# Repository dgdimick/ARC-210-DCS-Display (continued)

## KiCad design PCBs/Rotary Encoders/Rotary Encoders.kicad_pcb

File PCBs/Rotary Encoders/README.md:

# ARC-210 Rotary Encoder PCB

**Last updated: November 13, 2026 at 9:41 PM MST (America/Denver)**

Version **1.4 — Final PCB design**, updated October 12, 2026.

I finalized **PCB version 1.4 and checked its physical fit** on October 12, 2026.

Version 1.4 publishes the latest saved PCB layout and project settings, including the updated board outline and v1.4 silkscreen label. I ran fresh version 1.4 checks on October 27, 2026; see the manufacturing files section. The earlier version 1.3 results below are historical.

For version 1.3, I checked this six-encoder PCB against its schematic. The electrical check reported zero errors and warnings; the PCB check reported zero violations, zero unconnected pads and zero schematic parity issues under the project's saved check settings. Courtyard and certain footprint checks are disabled in those settings.

I printed the rotary-encoder STL and confirmed that it fits, and all six encoders worked together in the combined hardware test. Testing an assembled, manufactured PCB is still on my list. The checks above cover the PCB design.

## Assembly order

**Solder the 14-pin J1 header on the back of the PCB first.** The rotary encoders will block access to the header’s solder pads once they’re installed. Install and solder the encoders after the header is in place. **Line up all the encoder pins with their holes before pressing the encoder into the PCB.** The pins bend easily and can break if forced.

## Open the project

Download this folder and keep its contents together. Open `Rotary Encoders.kicad_pro` in KiCad 10. The custom symbol and footprint libraries are included and use project-relative paths. Install KiCad's standard symbol and footprint libraries as well.

## Required 3D-printed encoder spacers

Print **six** [Rotary Encoder spacers v.1](../../Supporting%20STL%27s/Rotary_Encoder_Spacer_v.1.stl), one per encoder. They center the encoder threads in the faceplate holes.

## Optional encoder 3D model

Download [LIB_PEC11H-4220F-S0024.zip](LIB_PEC11H-4220F-S0024.zip), the original supplier library archive. Extract `PEC11H-4220F-S0024/3D/PEC11H-4220F-S0024.stp` and place the STP file beside `Rotary Encoders.kicad_pcb`.

In KiCad PCB Editor, open each encoder's Footprint Properties → 3D Models and use `${KIPRJMOD}/PEC11H-4220F-S0024.stp`. Remove or disable the older `PEC11R-4220F-S0024.stp` substitute so two models are not displayed together. Use offset X = 2.5 mm, Y = 7.49 mm, Z = 0.2300 mm; scale = 1 on all axes; rotation X = 90°, Y = -180°, Z = -180°. Check alignment in the 3D Viewer. Make the same model change in the library footprint if you want it applied to future placements.

The STEP model is optional; missing 3D models do not prevent opening or manufacturing the board.

## Parts and connections

- Six Bourns PEC11H-4220F-S0024 rotary encoders.
- J1: 14-pin header; use the assigned footprint to choose the connector.
- Both J1 pins 13 and 14 connect to GND, as do encoder common contacts and metal mounting tabs.
- The encoders' push-switch contacts S1 and S2 are deliberately unused and marked no-connect.

| J1 pin | Connection |
| --- | --- |
| 1 | SW1 B |
| 2 | SW1 A |
| 3 | SW2 A |
| 4 | SW2 B |
| 5 | SW3 B |
| 6 | SW3 A |
| 7 | SW4 A |
| 8 | SW4 B |
| 9 | SW5 B |
| 10 | SW5 A |
| 11 | SW6 B |
| 12 | SW6 A |
| 13 | GND (encoder commons and mounting tabs) |
| 14 | GND (encoder commons and mounting tabs) |

The tested GPIO pairs, identified by the labels printed on the Teensy, are: SW1 = 16/17, SW2 = 28/29, SW3 = 20/21, SW4 = 22/23, SW5 = 24/25 and SW6 = 26/27. Ensure all encoder commons share Teensy GND. The final [combined hardware test HEX](../../Firmware/Test%20Code/ARC210_Final_Hardware_Test_v1.0_Teensy41.hex) provides counts and A/B diagnostics.

## Manufacturing files

Download [Rotary-Encoder-PCB-v1.4-Gerbers-Drill.zip](Manufacturing/Rotary-Encoder-PCB-v1.4-Gerbers-Drill.zip) for PCB fabrication. Generated October 27, 2026 from the published version **1.4** PCB using KiCad 10.0.7. [Individual Gerbers, drill files, drill maps, and check reports](Manufacturing/) are also included.

The ZIP contains seven Gerber X2 layers (front/back copper, solder mask, silkscreen, and Edge.Cuts), a Gerber job file, separate metric Excellon PTH/NPTH drill files, a drill report, and manufacturing notes. Both Gerbers and drills use the absolute origin without mirroring. The source specifies a two-layer, 1.6 mm board. Verified drill totals: **65 plated holes and zero non-plated holes**; the empty NPTH file is included intentionally.

Fresh checks reported **zero ERC violations, zero non-excluded DRC violations, zero unconnected items, and zero schematic/PCB parity issues** under the saved settings. Existing disabled checks remain in effect. Review the manufacturer's preview before ordering. Testing an assembled, manufactured PCB remains pending.

PCB licensing: CERN-OHL-P-2.0, as specified in the repository.

## Teensy GPIO labels and KiCad pin numbers

**Use the numbers printed on the Teensy (or the matching GPIO labels on your breakout adapter) when following the firmware and wiring instructions.** KiCad uses a separate set of pin/pad numbers for the Teensy symbol and its matching `teensy:Teensy41` footprint. These include power and ground connections, so they are not the same as GPIO numbers.

| Teensy printed label / firmware GPIO | KiCad U1 pin / footprint pad |
| --- | ---: |
| GND (one of several ground connections) | 1 |
| 0 | 2 |
| 4 — TFT backlight | 6 |
| 14 / A0 — rotary-switch input | 36 |
| 15 / A1 — rotary-switch input | 37 |

For example, connect a rotary-switch signal to the Teensy connection marked **14/A0**, which is **KiCad pad 36**—not pad 14. In KiCad, read the symbol’s pin name and net label to identify the signal. Updating the PCB from the schematic with the matching symbol and footprint maps the connections to the correct physical locations. This pad mapping applies to the Teensy library supplied with this project; other libraries may use different numbering.

## Estimated build cost

If you’re thinking about building one, the [DIY parts purchasing estimate](../../parts/README.md#estimated-build-cost) gives you an idea of the budget, including the faceplate, display, electronics, and PCB fabrication. I’ve included the files and build notes to help you put it together.

## Questions and community builds

If you have questions, ideas, or photos of your build, I’d love to hear from you. [GitHub Discussions](https://github.com/dgdimick/ARC-210-DCS-Display/discussions)

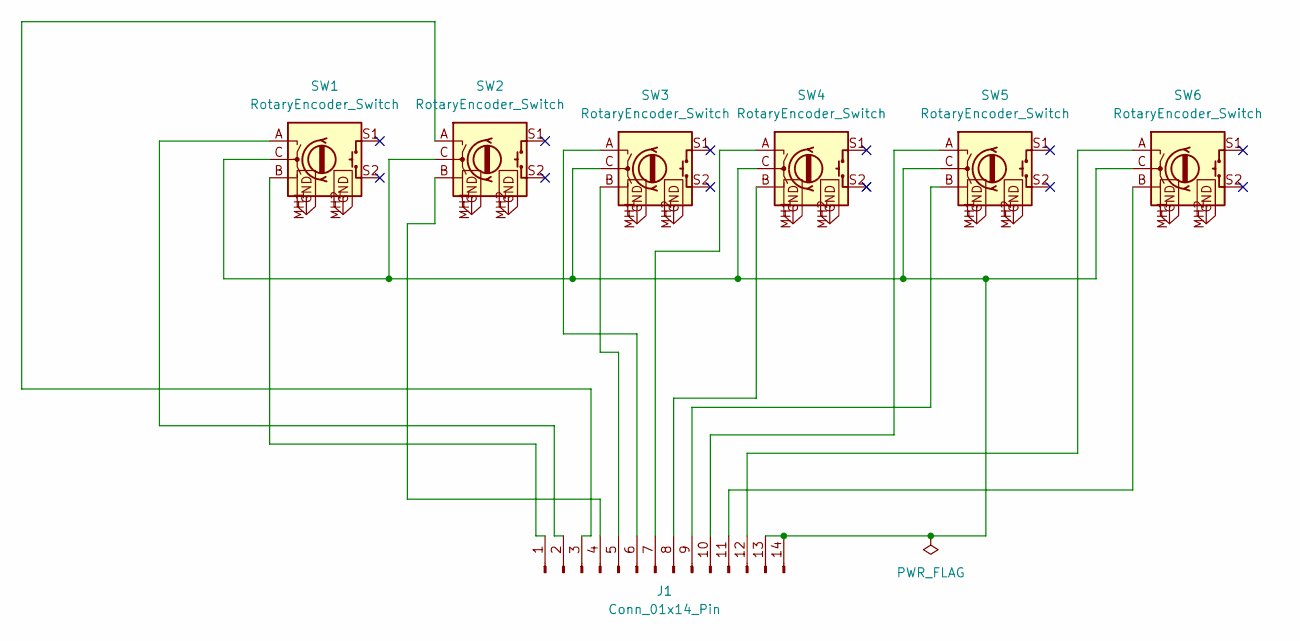
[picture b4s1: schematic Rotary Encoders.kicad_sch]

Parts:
J1: Conn_01x14_Pin; PinHeader_1x14_P2.54mm_Vertical
SW1, SW2, SW3, SW4, SW5, SW6: RotaryEncoder_Switch; PEC11H4220FS0024

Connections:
GND: SW1.MH1 (CASE), SW1.MH2 (CASE), SW2.MH1 (CASE), SW2.MH2 (CASE), SW3.MH1 (CASE), SW3.MH2 (CASE), SW4.MH1 (CASE), SW4.MH2 (CASE), SW5.MH1 (CASE), SW5.MH2 (CASE), SW6.MH1 (CASE), SW6.MH2 (CASE)
unnamed: J1.1, SW1.B
unnamed: J1.2, SW1.A
unnamed: J1.3, SW2.A
unnamed: J1.4, SW2.B
unnamed: J1.5, SW3.B
unnamed: J1.6, SW3.A
unnamed: J1.7, SW4.A
unnamed: J1.8, SW4.B
unnamed: J1.9, SW5.B
unnamed: J1.10, SW5.A
unnamed: J1.11, SW6.B
unnamed: J1.12, SW6.A
unnamed: J1.13, J1.14, SW1.C, SW2.C, SW3.C, SW4.C, SW5.C, SW6.C

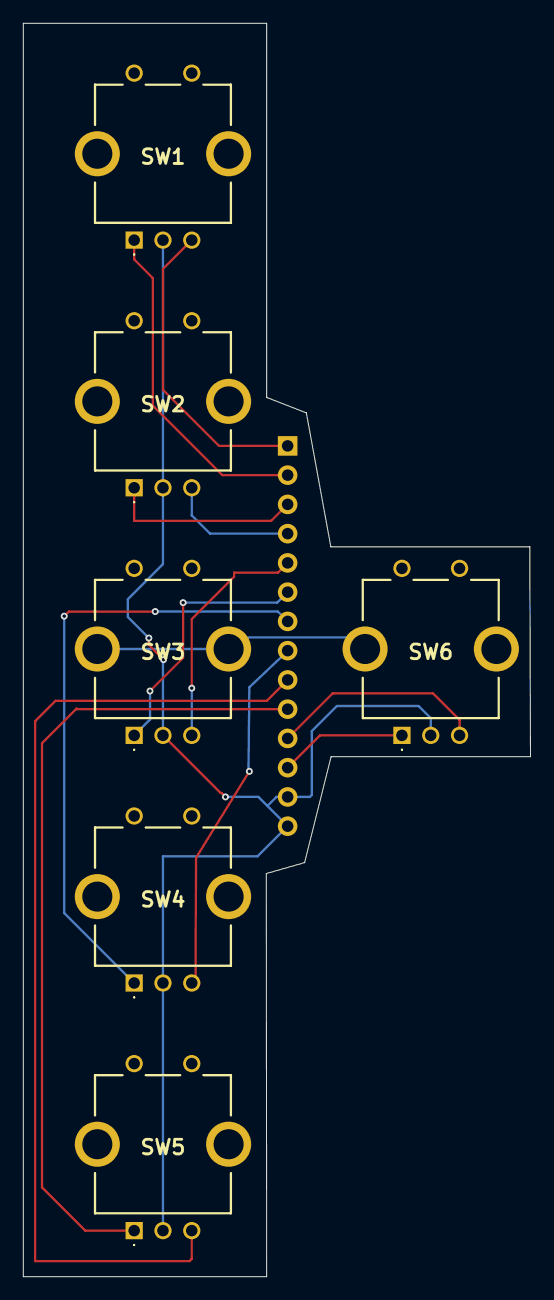
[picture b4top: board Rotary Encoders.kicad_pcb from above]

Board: 2 copper layers, 44.0 x 108.8 mm, 7 parts (1 on the bottom side), 14 nets.

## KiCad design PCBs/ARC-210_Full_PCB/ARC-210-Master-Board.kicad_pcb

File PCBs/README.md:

# ARC-210 PCBs

**Last updated: November 13, 2026 at 9:41 PM MST (America/Denver)**

Updated October 29, 2026.

## Buy a complete set of bare PCBs

See my [ARC-210 bare PCB offer and separate 3D-printing help](../Docs/ARC-210-Parts-Offers.md) for current prices, what’s included, materials, availability, shipping, VAT, and import charges. My bare PCB offer covers the ARC-210. I’ll offer printing help for the ARC-164 and ARC-186 once their printed parts are finalized. I’m happy to provide a free printed set whether you get your PCBs from me or elsewhere. Just cover shipping.

## No access to a 3D printer?

I offer separate 3D-printing help for builders whose lack of printer access is preventing their build. This supplies printed plastic only, not electronic components or a complete kit; buy the other components separately. See [ARC-210 3D-printing help](../Docs/ARC-210-Parts-Offers.md#printed-parts) for the current price, PETG colors, availability, shipping, VAT, and import-charge details.

## Estimated total build cost

I know the build cost may stretch some budgets. I’ve shared [my thoughts on the cost and development work](../parts/README.md#estimated-total-build-cost) in the parts list, including roughly 480 hours working on the code, hardware design, PCB design, and testing (about 8 hours a day) and US$500 in extra development parts. My development-time estimate includes work I did before I started using ChatGPT, as well as over 120 hours using ChatGPT and Codex to help with some of the more complex code. I’m sure my dog [Cody](../Docs/Cody%20not%20happy.jpg) isn’t happy about this.

My PCBs are designed around the faceplate and layout I’m using, so they may not fit someone else’s custom panel. I’m sharing the [source code](../Firmware/Source/Master_Program/README.md) so other builders can reuse it or adapt it to their own controls, displays, and wiring. Some changes may be needed, but I hope it gives people a useful starting point and saves them development time.

New aircraft support will require loading an updated HEX once; after that, I plan to switch between aircraft supported by that version without reflashing. This is still in development. See the [firmware version and aircraft-support plan](../Firmware/Master%20Hex%20Files/README.md).

Here are both PCB options using the same component estimates. These totals cover the panel’s parts, including the PC Flights faceplate, rather than just the bare boards. **All amounts are in US dollars (USD).**

**My PCB offer is for bare boards only.** Buy the electronic components, faceplate, and wiring separately. I’m happy to provide a free printed set whether you get your PCBs from me or elsewhere. Just cover shipping. See [what’s included and the shipping and fee details](../Docs/ARC-210-Parts-Offers.md). The build totals below cover separate DIY purchases, not a kit I sell.

| PCB purchasing option | PCB cost (USD) | Estimated full DIY build cost (USD) |
| --- | ---: | ---: |
| JLCPCB: five copies of each of four designs (20 bare boards, including spares) | US$58.20 cart estimate | US$267.72–US$300.72 |
| [My six bare PCBs only (no components)](../Docs/ARC-210-Parts-Offers.md#bare-pcb-set) | **US$40.00**, plus shipping and handling | **US$249.52–US$282.52**, before shipping, handling, and applicable fees |

For availability, what’s included in my set, and shipping/VAT/import-fee details, see [ARC-210 bare PCB offer and separate 3D-printing help](../Docs/ARC-210-Parts-Offers.md#both-pcb-purchasing-options). I’m happy to provide a free printed set whether you get your PCBs from me or elsewhere. Just cover shipping.

**My PCB-set option:** Shipping and handling are separate. I’ll only collect VAT if I’m required to; buyers may still owe import VAT, customs duties, or carrier fees even if I don’t collect VAT. Delivery and applicable fees for the other components are also separate. Compare the final delivered totals for your location.

**The US$58.20 PCB allowance uses the November 1, 2026 cart estimate: US$41.10 fabrication + US$32.10 estimated shipping − a US$15.00 coupon.** Shipping shown in that cart is already included; don’t add it twice. Coupon eligibility and shipping vary. If the US$15.00 coupon is unavailable, add US$15.00 to the JLCPCB-based estimate. Any duties, taxes, VAT, carrier fees, or other charges not included in that cart subtotal may still apply, as may delivery charges for the other components. Check your own final checkout total before ordering. These are estimates rather than fixed kit prices; the updated JLCPCB option rounds to about **US$268–US$301** for budgeting. Tools, labor, and cockpit mounting fasteners are excluded.

See the [parts-cost breakdown](../parts/README.md#estimated-build-cost) for component prices and allowances, and the [PCB manufacturing guide](../Docs/PCB-Manufacturing-JLCPCB.md) for the JLCPCB quote details. Compare the full delivered totals for your location before choosing how to buy the boards.

**SQL On/Off:** I use the **C&K A12515RNZQ solder-lug rotary switch**, with its stop ring set to **two positions for 45° total travel**. Align the knob with the panel’s ON/OFF markings. See the [parts list](../parts/README.md) for shaft-length and mounting details.

## PCB layout — five or six boards

The panel uses **five required PCBs**: one Main Board, one Button Matrix, one Rotary Encoder, and two multi-position Rotary Switch boards, all controlled by one Teensy 4.1. The **optional SQL On/Off PCB brings the total to six**; it can be omitted when wiring directly to the switch’s solder lugs. The SQL board uses the same Rotary Switch PCB design.

The [shaft spacer v.5](../Supporting%20STL%27s/Shaft_Spacer_v.5.stl) is **required in all installations** to support the longer SQL On/Off switch shaft, whether or not the optional PCB is fitted.

I’ve checked the physical fit of all four PCB designs, including the Button Matrix alignment:

| PCB | Final version | Status |
| --- | --- | --- |
| [Main Board](Master%20Board/) | 1.1 | Physical fit confirmed October 29, 2026; manufactured-board assembly and electrical testing pending |
| [Button Matrix](Button%20Matrix/) | 3.2 | Final design; v3.1 physical test fit and button alignment confirmed |
| [Rotary Encoders](Rotary%20Encoders/) | 1.4 | Final design; test fit confirmed |
| [Rotary Switches](Rotary%20Switches/) | 2.0 | Final design; test fit confirmed |

Use the KiCad project files in each linked folder. Each folder includes its wiring and assembly notes.

I’ve confirmed the mechanical fit of these designs. Testing an assembled, manufactured PCB is still on my list. Each project’s README explains the electrical checks and hardware tests completed so far.

## Required Rotary Encoder spacers

Print **six [Rotary Encoder spacers v.1](../Supporting%20STL%27s/Rotary_Encoder_Spacer_v.1.stl)**, one for each encoder, to center the encoder threads in the faceplate holes.

## Gerber and drill downloads

**Ordering for the first time?** My [JLCPCB manufacturing guide](../Docs/PCB-Manufacturing-JLCPCB.md) walks through ordering the bare boards from the manufacturer I use, including quantities, settings, and preview checks.

Button Matrix v3.2 manufacturing files generated October 30, 2026; other control-board files generated October 27, 2026; Main Board v1.1 files updated October 29, 2026:

| PCB | Version | Gerber and drill ZIP | Individual files and reports |
| --- | --- | --- | --- |
| Main Board | 1.1 | [Download ZIP](Master%20Board/Manufacturing/Main-Board-PCB-v1.1-Gerbers-Drill.zip) | [Browse files](Master%20Board/Manufacturing/) |
| Button Matrix | 3.2 | [Download ZIP](Button%20Matrix/Manufacturing/Button-Matrix-PCB-v3.2-Gerbers-Drill.zip) | [Browse files](Button%20Matrix/Manufacturing/) |
| Rotary Encoders | 1.4 | [Download ZIP](Rotary%20Encoders/Manufacturing/Rotary-Encoder-PCB-v1.4-Gerbers-Drill.zip) | [Browse files](Rotary%20Encoders/Manufacturing/) |
| Rotary Switches | 2.0 | [Download ZIP](Rotary%20Switches/Manufacturing/Rotary-Switch-PCB-v2.0-Gerbers-Drill.zip) | [Browse files](Rotary%20Switches/Manufacturing/) |

Each ZIP includes copper, solder-mask, silkscreen, and board-outline Gerbers, a Gerber job file, separate plated/non-plated Excellon drill files, a drill report, and manufacturing notes. Drill maps and ERC/DRC reports are available in each manufacturing folder.

Review the manufacturer's preview before ordering. The Button Matrix's printed fit check confirmed button alignment, and its slightly long edges were shortened for final v3.1. Manufactured-board testing remains pending for all four designs. Existing check exclusions and disabled categories are documented in the individual project READMEs and reports.

## Button Matrix PCB — version 3.2

**The current Button Matrix PCB v3.2 does not support LED backlighting.** I would need to redesign the button board with LED support, use suitable light-transmitting buttons, and make the required Main Board, power, and driver changes. I may revisit this after completing the ARC-164 and ARC-186 projects; there is no finished backlit button-board design or release date yet. See [Future Thoughts](../Docs/Future-Thoughts.md) for the lighting redesign plan.

**October 30, 2026:** v3.2 removes the duplicate SQL hole outline, retains the 12 mm NPTH, updates revision markings, and moves H3’s reference clear of the mask opening. Fresh KiCad exports and ERC/DRC checks pass under saved settings. No electrical changes; manufactured-board testing remains pending. The v3.1 notes below record the earlier outline and physical-fit work.

**Final design; v3.1 test fit confirmed — October 27, 2026:** The printed fit check confirmed that the buttons are correctly positioned. The slightly long board edges were shortened, and version **3.1** replaced v3.0 before the v3.2 hole correction. The physical test fit of the revised v3.1 board is confirmed. The updated KiCad and manufacturing files are uploaded.

The current unlit 16-button, 4 × 4 Button Matrix PCB is **version 3.2**. See the [Button Matrix README](Button%20Matrix/README.md) for front and back layout previews. The front carries the push-button switches; the back carries the matrix diodes and row/column connectors. A 12 mm pass-through provides clearance for the SQL On/Off switch.

The downloadable [version 3.2 KiCad files](Button%20Matrix/) now include the PCB layout, schematic, project settings, and custom 12 mm footprint library. The PCB includes routing; unused floating copper fills were removed. Checks found zero ERC violations, zero DRC errors, no unconnected items, and no schematic/PCB parity issues; DRC also reports zero warnings after removal of those fills. Physical fit and button alignment have been checked; manufactured-board assembly and electrical testing remain pending. A backlit version would require a redesigned button board; it is a possible future project, with no finished design or release date.

## Main Board PCB v1.1 and schematic

**Layout progress — October 28, 2026:** Component placement and routing are progressing on the Main Board. The [new Main Board layout picture](../images/Main-PCB-Layout-2026-10-28.png) shows the Teensy 4.1, TFT and control connectors, SQL On/Off solder connections, and back-side component arrangement. J9 is labelled **MODE** and J10 **MASTER**. A 26.2 mm circle provides a SQL switch body spacing guide without electrical pads. The rotary-switch mounting opening, anti-rotation slot, and four 3.5 mm mounting holes remain.

The current saved Main Board PCB and schematic have now been uploaded to match the layout-progress picture. October 29 checks after correcting the J4/TP1 values report zero ERC violations, zero DRC violations, zero unconnected items, and zero schematic/PCB mismatches under the saved settings. See the [Main Board README and picture](Master%20Board/README.md#main-pcb-3d-preview) and [3D Viewer instructions](Master%20Board/README.md#teensy-41-in-the-3d-viewer). I’ve checked the physical fit of Main Board v1.1. Final placement/routing review and current verification remain to be completed; the October 29 ERC/DRC and parity checks pass under the saved settings. Main Board v1.1 Gerber and drill files are now available above; physical fit is confirmed and manufactured-board testing remains pending.

The updated [Main Board PCB draft, schematic, and KiCad project](Master%20Board/) are available to download. The board now uses USB power and the Teensy's 3.3 V supply for TFT VCC; the external protected 5 V branch and power selector are removed. C5/C6 have been removed to match the tested direct TFT wiring; C1/C2 rotary-input filters remain. I’ve tested the TFT at 3.3 V and found the brightness satisfactory. Components are on B.Cu, facing away from the faceplate. The draft has zero unconnected items under the October 29 checks. I’ve checked the physical fit of Main Board v1.1. Final placement/routing review and current verification remain pending; Main Board v1.1 manufacturing files are provided above.

## Teensy GPIO labels and KiCad pin numbers

**Use the numbers printed on the Teensy (or the matching GPIO labels on your breakout adapter) when following the firmware and wiring instructions.** KiCad uses a separate set of pin/pad numbers for the Teensy symbol and its matching `teensy:Teensy41` footprint. These include power and ground connections, so they are not the same as GPIO numbers.

| Teensy printed label / firmware GPIO | KiCad U1 pin / footprint pad |
| --- | ---: |
| GND (one of several ground connections) | 1 |
| 0 | 2 |
| 4 — TFT backlight | 6 |
| 14 / A0 — rotary-switch input | 36 |
| 15 / A1 — rotary-switch input | 37 |

For example, connect a rotary-switch signal to the Teensy connection marked **14/A0**, which is **KiCad pad 36**—not pad 14. In KiCad, read the symbol’s pin name and net label to identify the signal. Updating the PCB from the schematic with the matching symbol and footprint maps the connections to the correct physical locations. This pad mapping applies to the Teensy library supplied with this project; other libraries may use different numbering.

## Power and future button lighting

The painted buttons supplied with the PC Flights panel used for this build are opaque: light will not pass through them, so LEDs behind them would not illuminate their legends. Future backlighting would also require suitable light-transmitting replacement buttons.

The Teensy is powered by USB, and **TFT VCC connects directly to the Teensy's 3.3 V rail** (`TEENSY_3V3`, U1 pad 15). I’ve tested the TFT at 3.3 V and found the brightness satisfactory. I removed the external protected 5 V input and Main Board JP1 power selector. I removed C5 (470 µF) and C6 (0.1 µF) to match the direct Teensy-to-TFT wiring I tested. C1/C2 and R1/R2 remain as the rotary-input filters. Keep total external 3.3 V consumption within PJRC's recommended 250 mA maximum; brightness confirmation is not a current measurement.

**The current Button Matrix PCB v3.2 does not support LED backlighting.** I would need to redesign it and the Main Board and use light-transmitting buttons. There is no finished design or release date. The TFT backlight is separate; see [Future Thoughts](../Docs/Future-Thoughts.md) for clearance, power, possible four-layer costs, and reusable-part plans.

I recommend using **male pin headers on the Teensy and matching female socket strips on the Main Board** so the controller can be unplugged. If I release a compatible replacement Main Board, you could move your existing Teensy to it rather than buy another controller, saving some money. Soldering the Teensy’s header pins directly into the Main Board does not provide that removable connection.

I hope to reuse the controls, socket-mounted Teensy, and faceplate in a future lighting upgrade, subject to compatibility checks. Replacement boards may need four layers and cost more; I have no finished design or release date. See [Future Thoughts](../Docs/Future-Thoughts.md).

## Optional SQL On/Off PCB

The SQL On/Off PCB is optional when wiring directly to the switch’s solder lugs. The build uses five PCBs without it, or six with it. Dedicated **TP1 (SQL signal, GPIO 41 / U1 pad 33)** and **TP2 (GND)** solder-wire pads are now included in the Main Board schematic and PCB draft. The optional SQL1 header remains available. The pads are placed and routed in the current draft; I’ve checked the physical fit of Main Board v1.1; I still need to check the assembled board. See the [direct-wiring notes](../parts/README.md#six-pcb-layout) for details.

The [shaft spacer v.5](../Supporting%20STL%27s/Shaft_Spacer_v.5.stl) is **required in all installations** to support the **longer SQL On/Off switch shaft**, whether using the optional switch PCB or wiring directly to the switch’s solder lugs.

## Channel and SQL knobs

**The 17-part set has passed test fitting at 100% scale, with Channel v4.2 separately reprinted and confirmed after the earlier complete-layout test. The combined downloads now include that replacement.** Please keep checking [Project Updates](../Docs/Project-Updates.md) for changes.

[Channel knob v4.2](../Supporting%20STL%27s/Channel_Knob_v.4.2.stl) · [SQL knob v1.2](../Supporting%20STL%27s/SQL_Knob_v.1.2.stl)

**Channel v4.2 and SQL v1.2 have the same outside size and small side hole, but different shaft holes.** Print one of each at 100% scale. I’ve test-fitted both; see the [STL README](../Supporting%20STL%27s/README.md) for the socket details and current downloads.

The SQL shaft support spacer v.5 remains required in all installations.

## Estimated build cost

If you’re thinking about building one, the [DIY parts purchasing estimate](../parts/README.md#estimated-build-cost) gives you an idea of the budget, including the faceplate, display, electronics, and PCB fabrication. I’ve included the files and build notes to help you put it together.

## Sharing code and improvements

My main firmware code is shared under the [MIT License](../Docs/LICENSE-MIT.txt), and I’m happy to provide it to anyone who asks. You can also find the [published source here](../Firmware/Source/Master_Program/README.md). If you adapt it or add improvements, I’d love to work with you and bring useful changes back into this project so other builders—and my other panel projects—can benefit too.

Please share your changes through a pull request or get in touch in [Discussions](https://github.com/dgdimick/ARC-210-DCS-Display/discussions). I welcome contributions. The linked MIT License explains the terms for using and sharing the code. Third-party code keeps its own license. The PCB designs retain their separate hardware license.

## Questions and community builds

If you have questions, ideas, or photos of your build, I’d love to hear from you. [GitHub Discussions](https://github.com/dgdimick/ARC-210-DCS-Display/discussions)

### Main Board v1.1 fabrication export

The current [Main Board Gerber/drill ZIP](Master%20Board/Manufacturing/Main-Board-PCB-v1.1-Gerbers-Drill.zip) is available, including the USB zip-tie slots. This standalone two-layer, 1.6 mm v1.1 export includes the ground pours. Main Board v1.1 physical fit is confirmed; current verification and electrical testing remain pending. See the [Main Board README](Master%20Board/README.md#standalone-manufacturing-files).

Main Board **v1.1** includes GND-connected copper pours on both layers, with isolated islands removed. Use its updated [v1.1 fabrication package](Master%20Board/Manufacturing/Main-Board-PCB-v1.1-Gerbers-Drill.zip).

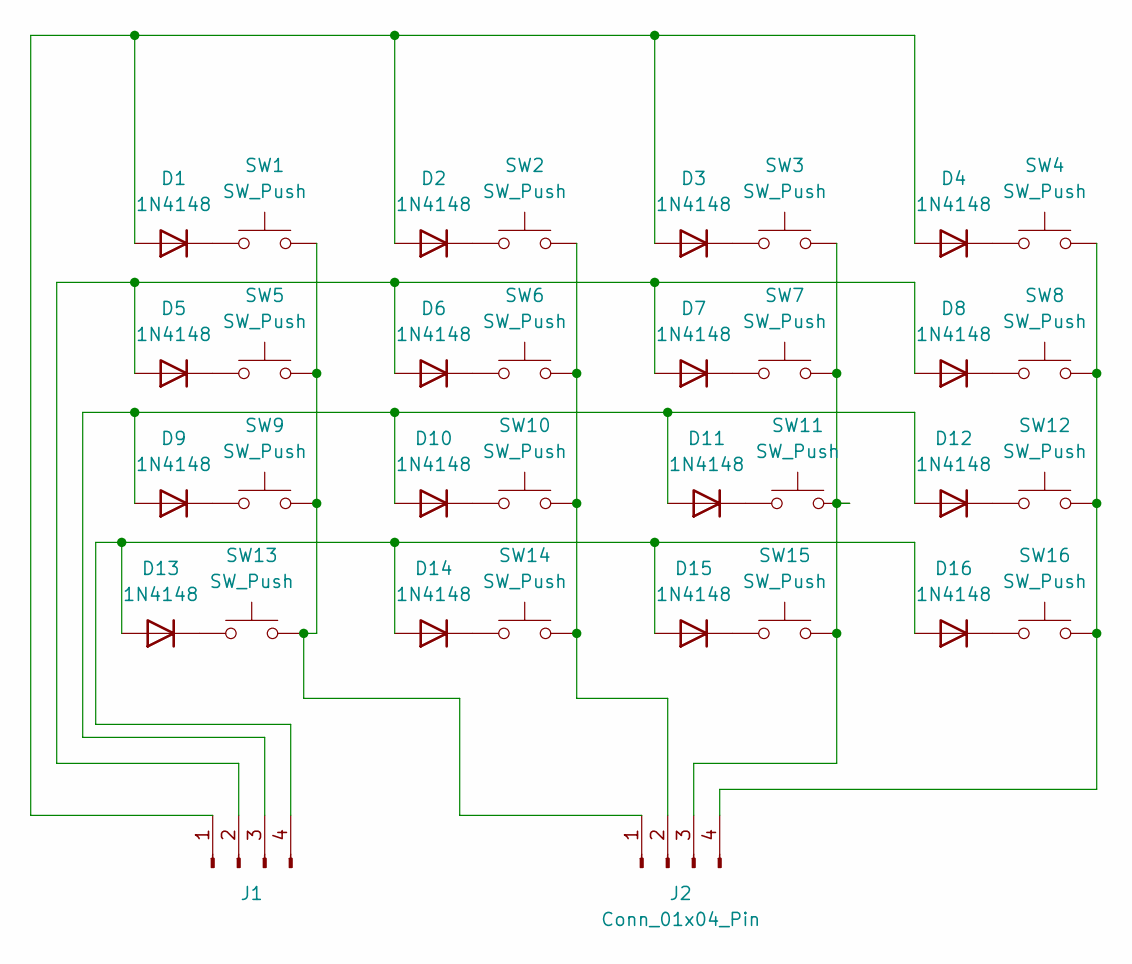
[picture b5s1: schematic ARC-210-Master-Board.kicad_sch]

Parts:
D1, D2, D3, D4, D5, D6, D7, D8, D9, D10, D11, D12, D13, D14, D15, D16: 1N4148; D_DO-35_SOD27_P7.62mm_Horizontal
J1, J2: Conn_01x04_Pin; PinHeader_1x04_P2.54mm_Vertical
SW1, SW2, SW3, SW4, SW5, SW6, SW7, SW8, SW9, SW10, SW11, SW12, SW13, SW14, SW15, SW16: SW_Push; SW_PUSH_6mm_H5mm

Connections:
unnamed: D1.2 (A), D2.2 (A), D3.2 (A), D4.2 (A), J1.1
unnamed: D1.1 (K), SW1.1
unnamed: D2.1 (K), SW2.1
unnamed: D3.1 (K), SW3.1
unnamed: D4.1 (K), SW4.1
unnamed: D5.2 (A), D6.2 (A), D7.2 (A), D8.2 (A), J1.2
unnamed: D5.1 (K), SW5.1
unnamed: D6.1 (K), SW6.1
unnamed: D7.1 (K), SW7.1
unnamed: D8.1 (K), SW8.1
unnamed: D9.1 (K), SW9.1
unnamed: D9.2 (A), D10.2 (A), D11.2 (A), D12.2 (A), J1.3
unnamed: D10.1 (K), SW10.1
unnamed: D11.1 (K), SW11.1
unnamed: D12.1 (K), SW12.1
unnamed: D13.2 (A), D14.2 (A), D15.2 (A), D16.2 (A), J1.4
unnamed: D13.1 (K), SW13.1
unnamed: D14.1 (K), SW14.1
unnamed: D15.1 (K), SW15.1
unnamed: D16.1 (K), SW16.1
unnamed: J2.1, SW1.2, SW5.2, SW9.2, SW13.2
unnamed: J2.2, SW2.2, SW6.2, SW10.2, SW14.2
unnamed: J2.3, SW3.2, SW7.2, SW11.2, SW15.2
unnamed: J2.4, SW4.2, SW8.2, SW12.2, SW16.2

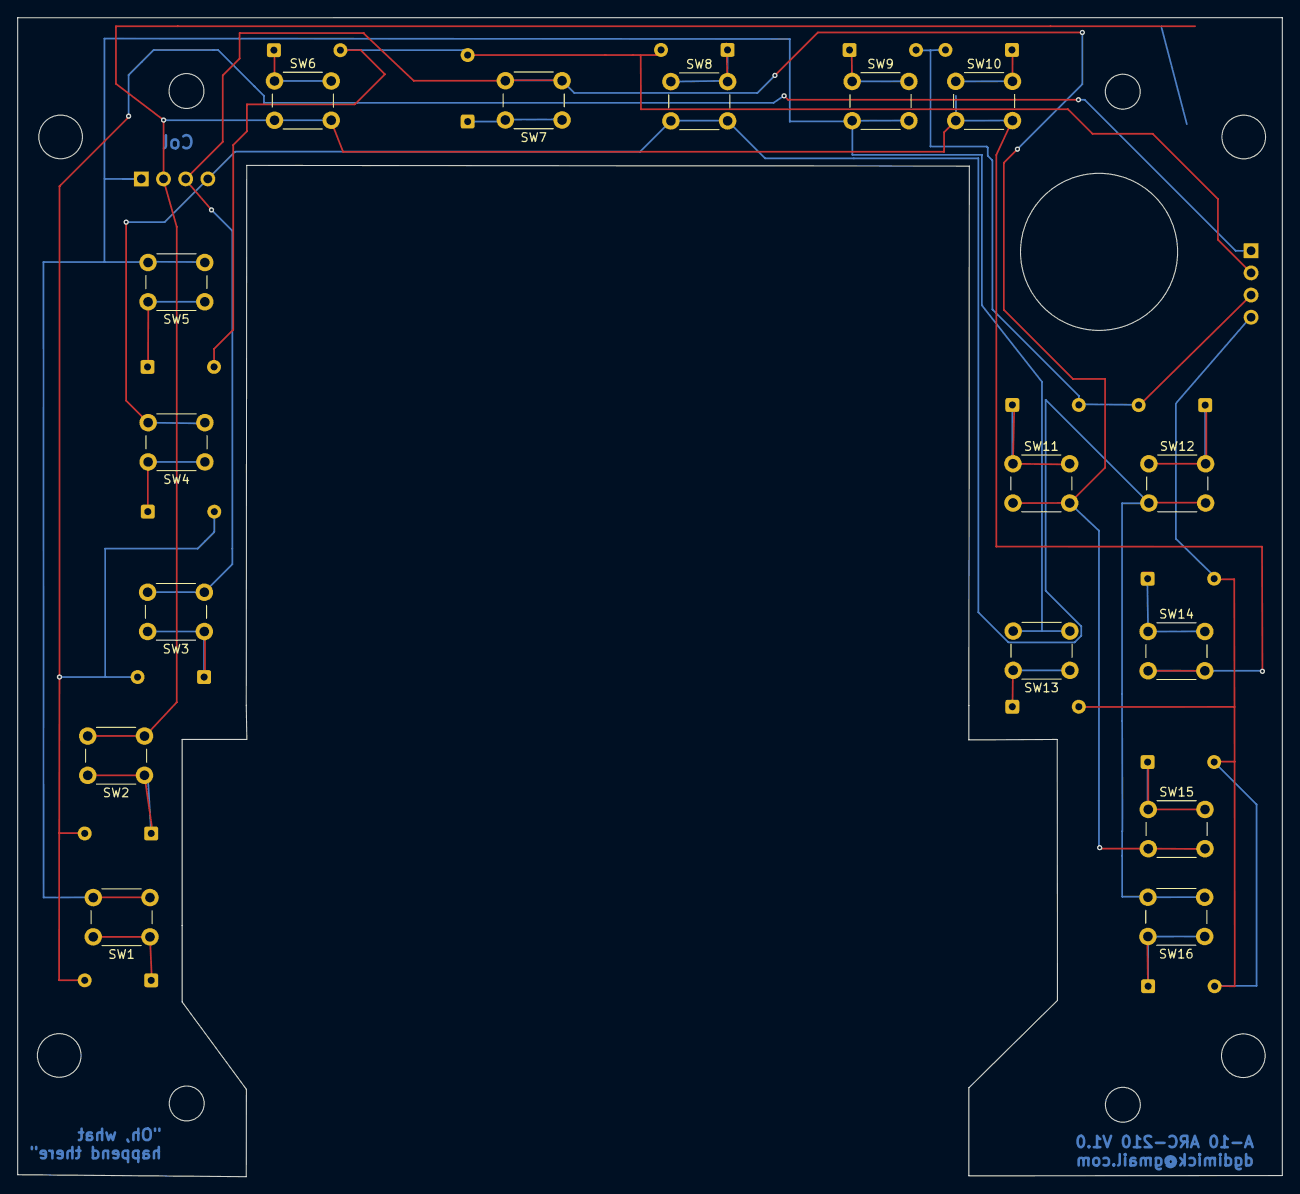
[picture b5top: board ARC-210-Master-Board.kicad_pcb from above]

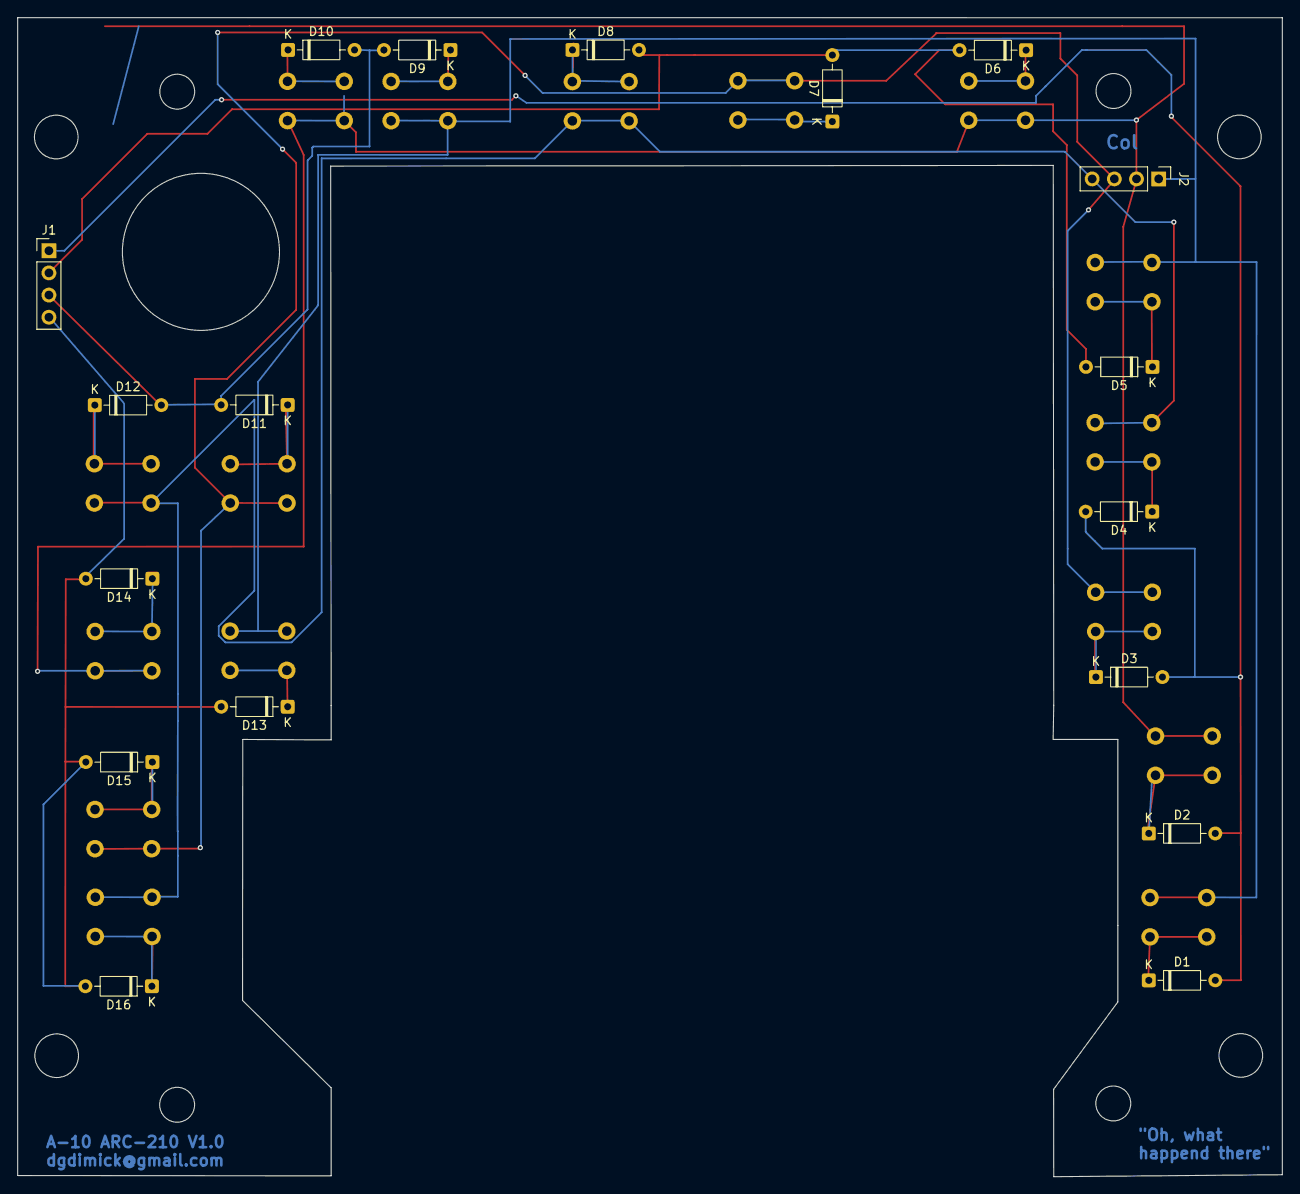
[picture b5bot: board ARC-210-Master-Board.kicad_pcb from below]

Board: 2 copper layers, 144.9 x 132.8 mm, 34 parts (18 on the bottom side), 24 nets.
